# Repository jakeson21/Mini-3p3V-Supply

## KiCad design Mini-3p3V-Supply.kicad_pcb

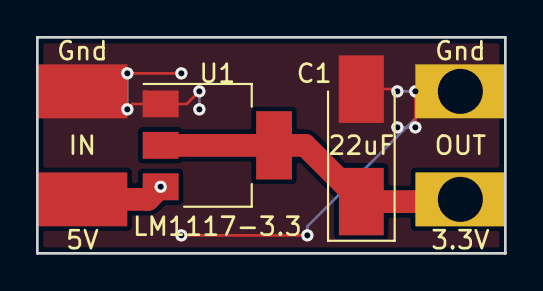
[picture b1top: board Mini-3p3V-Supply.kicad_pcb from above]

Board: 2 copper layers, 26.0 x 12.0 mm, 7 parts (1 on the bottom side), 3 nets.

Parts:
C1: 22uF; CP_Tantalum_Case-C_EIA-6032-28_Hand
J1: 5V; SolderPad3x5NoDrill
J2: Gnd; SolderPad3x5NoDrill
J3: 3.3V; SolderPad3x5
J4: Gnd; SolderPad3x5
J5: USB_OTG; USB_Micro_B_FCI_10118192_HandSolder
U1: LM1117-3.3; SOT-223-3_TabPin2

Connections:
+3V3: C1.1, J3.1, U1.2
+5V: J1.1, J5.1, U1.3
GND: C1.2, J2.1, J4.1, J5.5, J5.6, U1.1

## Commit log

2018-09-21 Initial version
2019-11-21 It works
